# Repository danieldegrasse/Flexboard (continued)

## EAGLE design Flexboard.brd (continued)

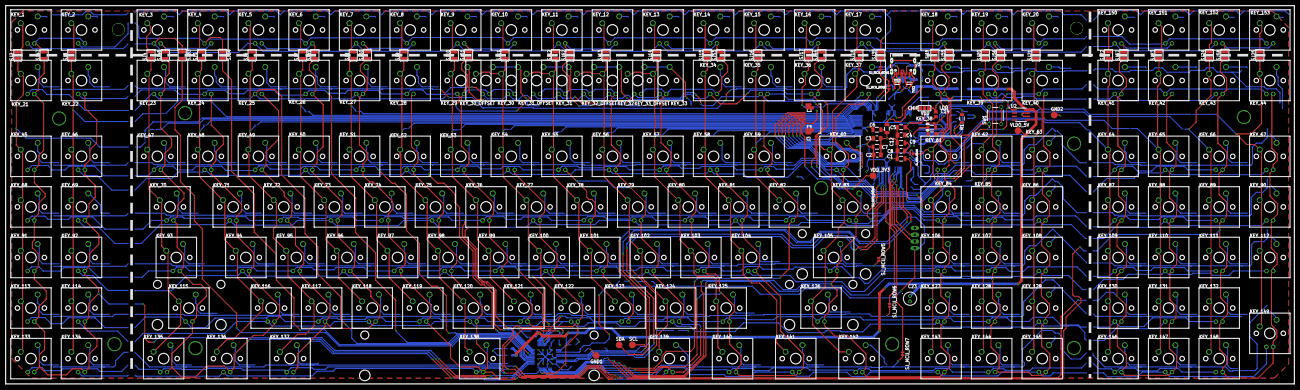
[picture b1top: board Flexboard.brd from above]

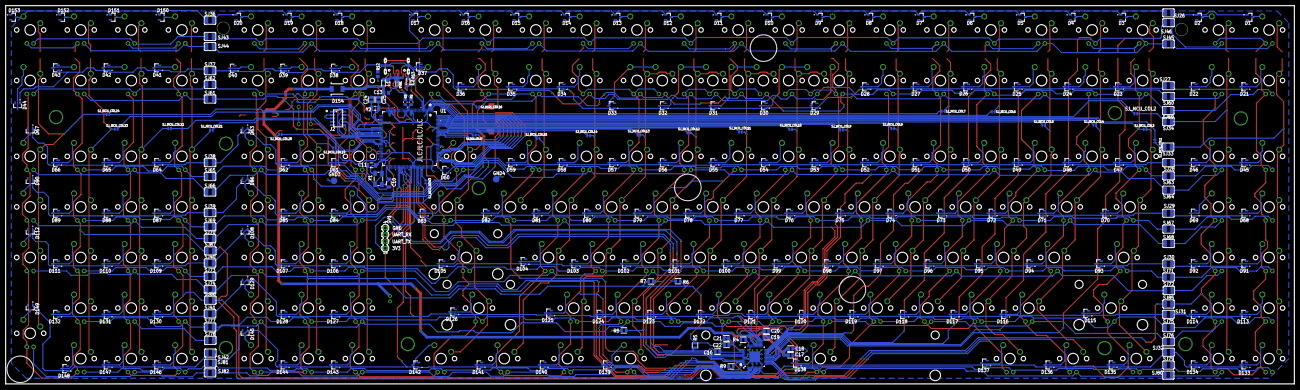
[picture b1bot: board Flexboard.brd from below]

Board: 2 copper layers, 485.5 x 142.5 mm, 498 parts (258 on the bottom side), 367 nets.

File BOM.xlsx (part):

Part | Value | Device | Package | Description | AVAILABILITY | CATEGORY | COMMENT | CONFIGURATION_POLE-THROW | CONTACT_CURRENT_RATING | CPU | DESCRIPTION | DIGI-KEY_PART_NUMBER | EU_ROHS_COMPLIANCE | FLASHKB | MANUFACTURER | MANUFACTURER_PART_NUMBER | MAXFREQUENCY | MF | MP | MPN | OC_FARNELL | OC_NEWARK | OPERATING_TEMP | PACKAGE | PART_STATUS | PINCOUNT | POPULARITY | POWER_RATING | PRICE | PURCHASE-URL | RATING | RESISTANCE | ROHS_COMPLIANT | SERIES | SRAMKB | SUB-CATEGORY | THERMALLOSS | TOLERANCE | TP_SIGNAL_NAME | TYPE | VENDOR | VOLTAGE_RATING
C1 | 1000pF | C1206C102K1RACAUTO | CAPC3216X110N | Cap Ceramic 0.001uF 100V X7R 10% SMD 1206 125°C Plastic T/R Check availability | In Stock |  |  |  |  |  | 1000 pF ±10% 100V Ceramic Capacitor X7R 1206 (3216 Metric) |  |  |  |  |  |  | KEMET | C1206C102K1RACAUTO |  |  |  |  | 1206 KEMET |  |  |  |  | None | https://pricing.snapeda.com/search/part/C1206C102K1RACAUTO/?ref=eda
C2 | 1uF | GCM31MR71H105KA55L | CAPC3216X125N | None Check availability | In Stock |  |  |  |  |  | SMD Capacitor X7R(EIA) with Capacitance: 1.0uF Tol. 10%. Rated Voltage: 50Vdc |  |  |  |  |  |  | Murata | GCM31MR71H105KA55L |  |  |  |  | 1206 Murata |  |  |  |  | None | https://pricing.snapeda.com/search/part/GCM31MR71H105KA55L/?ref=eda
C3 | 1uF | GCM31MR71H105KA55L | CAPC3216X125N | None Check availability | In Stock |  |  |  |  |  | SMD Capacitor X7R(EIA) with Capacitance: 1.0uF Tol. 10%. Rated Voltage: 50Vdc |  |  |  |  |  |  | Murata | GCM31MR71H105KA55L |  |  |  |  | 1206 Murata |  |  |  |  | None | https://pricing.snapeda.com/search/part/GCM31MR71H105KA55L/?ref=eda
C4 | 1uF | GCM31MR71H105KA55L | CAPC3216X125N | None Check availability | In Stock |  |  |  |  |  | SMD Capacitor X7R(EIA) with Capacitance: 1.0uF Tol. 10%. Rated Voltage: 50Vdc |  |  |  |  |  |  | Murata | GCM31MR71H105KA55L |  |  |  |  | 1206 Murata |  |  |  |  | None | https://pricing.snapeda.com/search/part/GCM31MR71H105KA55L/?ref=eda
C5 | 100nF | C1206C104K5RAC7800 | CAPC3216X88N | Cap Ceramic 0.1uF 50V X7R 10% SMD 1206 125C Plastic T/R Check availability | In Stock |  |  |  |  |  | 0.1 µF ±10% 50V Ceramic Capacitor X7R 1206 (3216 Metric) |  |  |  |  |  |  | KEMET | C1206C104K5RAC7800 |  |  |  |  | 3216 KEMET |  |  |  |  | None | https://pricing.snapeda.com/search/part/C1206C104K5RAC7800/?ref=eda
C6 | 100nF | C1206C104K5RAC7800 | CAPC3216X88N | Cap Ceramic 0.1uF 50V X7R 10% SMD 1206 125C Plastic T/R Check availability | In Stock |  |  |  |  |  | 0.1 µF ±10% 50V Ceramic Capacitor X7R 1206 (3216 Metric) |  |  |  |  |  |  | KEMET | C1206C104K5RAC7800 |  |  |  |  | 3216 KEMET |  |  |  |  | None | https://pricing.snapeda.com/search/part/C1206C104K5RAC7800/?ref=eda
C7 | 100nF | C1206C104K5RAC7800 | CAPC3216X88N | Cap Ceramic 0.1uF 50V X7R 10% SMD 1206 125C Plastic T/R Check availability | In Stock |  |  |  |  |  | 0.1 µF ±10% 50V Ceramic Capacitor X7R 1206 (3216 Metric) |  |  |  |  |  |  | KEMET | C1206C104K5RAC7800 |  |  |  |  | 3216 KEMET |  |  |  |  | None | https://pricing.snapeda.com/search/part/C1206C104K5RAC7800/?ref=eda
C8 | 1uF | GCM31MR71H105KA55L | CAPC3216X125N | None Check availability | In Stock |  |  |  |  |  | SMD Capacitor X7R(EIA) with Capacitance: 1.0uF Tol. 10%. Rated Voltage: 50Vdc |  |  |  |  |  |  | Murata | GCM31MR71H105KA55L |  |  |  |  | 1206 Murata |  |  |  |  | None | https://pricing.snapeda.com/search/part/GCM31MR71H105KA55L/?ref=eda
C9 | 100nF | C1206C104K5RAC7800 | CAPC3216X88N | Cap Ceramic 0.1uF 50V X7R 10% SMD 1206 125C Plastic T/R Check availability | In Stock |  |  |  |  |  | 0.1 µF ±10% 50V Ceramic Capacitor X7R 1206 (3216 Metric) |  |  |  |  |  |  | KEMET | C1206C104K5RAC7800 |  |  |  |  | 3216 KEMET |  |  |  |  | None | https://pricing.snapeda.com/search/part/C1206C104K5RAC7800/?ref=eda
C10 | 22pF | C1206C220JGGAC7800 | CAPC3216X110N | Check availability | In Stock |  |  |  |  |  | CAP CER 22PF 2KV NP0 1206 |  |  |  |  |  |  | KEMET | C1206C220JGGAC7800 |  |  |  |  | 3216 KEMET |  |  |  |  | None
C11 | 22pF | C1206C220JGGAC7800 | CAPC3216X110N | Check availability | In Stock |  |  |  |  |  | CAP CER 22PF 2KV NP0 1206 |  |  |  |  |  |  | KEMET | C1206C220JGGAC7800 |  |  |  |  | 3216 KEMET |  |  |  |  | None
C12 | 2.2uF | 1206ZC225MAT2A | CAPC3216X178N | CERAMIC CAPACITOR, 2.2UF, 10V, X7R, 20%, 1206, FULL REEL Check availability | In Stock |  |  |  |  |  | 2.2 µF ±20% 10V Ceramic Capacitor X7R 1206 (3216 Metric) |  |  |  |  |  |  | AVX | 1206ZC225MAT2A |  |  |  |  | 3216 AVX |  |  |  |  | None | https://pricing.snapeda.com/search/part/1206ZC225MAT2A/?ref=eda
C13 | 10uF | GRM21BC8YA106ME11L | CAPC2012X145N | Cap Ceramic 10uF 35V X6S 20% Pad SMD 0805 105C T/R |  |  |  |  |  |  | 0805 10 uF 35 V ±20% Tolerance X6S Multilayer Ceramic Capacitor | 490-10505-2-ND |  |  |  |  |  | Murata | GRM21BC8YA106ME11L |  |  |  |  | 2012 Murata |  |  |  |  |  | https://pricing.snapeda.com/search/part/GRM21BC8YA106ME11L/?ref=eda
C14 | 10uF | GRM21BC8YA106ME11L | CAPC2012X145N | Cap Ceramic 10uF 35V X6S 20% Pad SMD 0805 105C T/R |  |  |  |  |  |  | 0805 10 uF 35 V ±20% Tolerance X6S Multilayer Ceramic Capacitor | 490-10505-2-ND |  |  |  |  |  | Murata | GRM21BC8YA106ME11L |  |  |  |  | 2012 Murata |  |  |  |  |  | https://pricing.snapeda.com/search/part/GRM21BC8YA106ME11L/?ref=eda
C15 | 1000pF | C1206C102K1RACAUTO | CAPC3216X110N | Cap Ceramic 0.001uF 100V X7R 10% SMD 1206 125°C Plastic T/R Check availability | In Stock |  |  |  |  |  | 1000 pF ±10% 100V Ceramic Capacitor X7R 1206 (3216 Metric) |  |  |  |  |  |  | KEMET | C1206C102K1RACAUTO |  |  |  |  | 1206 KEMET |  |  |  |  | None | https://pricing.snapeda.com/search/part/C1206C102K1RACAUTO/?ref=eda
C16 | 0.47uF | C_CHIP-0805(2012-METRIC) | CAPC2012X110 | Capacitor - Generic |  | Capacitor
C17 | 0.47uF | C_CHIP-0805(2012-METRIC) | CAPC2012X110 | Capacitor - Generic |  | Capacitor
C18 | 0.1uF | C_CHIP-0805(2012-METRIC) | CAPC2012X110 | Capacitor - Generic |  | Capacitor
C19 | 0.47uF | C_CHIP-0805(2012-METRIC) | CAPC2012X110 | Capacitor - Generic |  | Capacitor
C20 | 0.1uF | C_CHIP-0805(2012-METRIC) | CAPC2012X110 | Capacitor - Generic |  | Capacitor
C21 | 0.47uF | C_CHIP-0805(2012-METRIC) | CAPC2012X110 | Capacitor - Generic |  | Capacitor
C22 | 0.1uF | C_CHIP-0805(2012-METRIC) | CAPC2012X110 | Capacitor - Generic |  | Capacitor
C23 | 22uF | 860020672011 | 860020672011 | 22uF 50V Electrolytic Capacitor Wurth 860020672011
C24 | 12pF | C_CHIP-0805(2012-METRIC) | CAPC2012X110 | Capacitor - Generic |  | Capacitor
C25 | 12pF | C_CHIP-0805(2012-METRIC) | CAPC2012X110 | Capacitor - Generic |  | Capacitor
D1 | BAS16LT3G | BAS16LT3G | SOT95P240X111-3N | Diode Small Signal Switching 100V 0.2A Automotive 3-Pin SOT-23 T/R Check prices | In Stock |  |  |  |  |  | Diode Standard 100V 200mA (DC) Surface Mount SOT-23-3 (TO-236) |  |  |  |  |  |  | ON Semiconductor | BAS16LT3G |  |  |  |  | SOT-23-3 ON Semiconductor |  |  |  |  | None
D2 | BAS16LT3G | BAS16LT3G | SOT95P240X111-3N | Diode Small Signal Switching 100V 0.2A Automotive 3-Pin SOT-23 T/R Check prices | In Stock |  |  |  |  |  | Diode Standard 100V 200mA (DC) Surface Mount SOT-23-3 (TO-236) |  |  |  |  |  |  | ON Semiconductor | BAS16LT3G |  |  |  |  | SOT-23-3 ON Semiconductor |  |  |  |  | None
D3 | BAS16LT3G | BAS16LT3G | SOT95P240X111-3N | Diode Small Signal Switching 100V 0.2A Automotive 3-Pin SOT-23 T/R Check prices | In Stock |  |  |  |  |  | Diode Standard 100V 200mA (DC) Surface Mount SOT-23-3 (TO-236) |  |  |  |  |  |  | ON Semiconductor | BAS16LT3G |  |  |  |  | SOT-23-3 ON Semiconductor |  |  |  |  | None
D4 | BAS16LT3G | BAS16LT3G | SOT95P240X111-3N | Diode Small Signal Switching 100V 0.2A Automotive 3-Pin SOT-23 T/R Check prices | In Stock |  |  |  |  |  | Diode Standard 100V 200mA (DC) Surface Mount SOT-23-3 (TO-236) |  |  |  |  |  |  | ON Semiconductor | BAS16LT3G |  |  |  |  | SOT-23-3 ON Semiconductor |  |  |  |  | None
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
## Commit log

2021-07-25 Initial Commmit: Laid out keys in schematic
2021-07-25 Partially routed schematic. Pattern should duplicate for rest of board.
2021-07-26 Finished schematic wiring for PCB
2021-07-28 Switches laid out, some alignment needs fixing
2021-07-28 Fixed switch alignments
2021-07-28 Routed columns
2021-07-28 Added first few row routes
2021-08-05 Finished routing keyboard switches and diodes
2021-10-04 Routed LED ROW nets
    PCB has not had led traces routed, but LED row nets are routed in
    schematic
2021-10-04 Routed Column Nets for LEDs
    No LED traces routed on board, but all nets are routed for columns and
    rows in schematic
2021-10-04 Solder joints for LEDs laid out on board
2021-10-04 Working on moving rows to bottom layer
2021-10-04 Revert "Working on moving rows to bottom layer"
    This reverts commit 131a86a1cb6fe059613502008a9fd4c9c1a2df1a.
    Decided it was best to leave diodes on top, so that the chip would have
    more space to route in
2021-10-04 Routed LED columns, rows partially routed
2021-10-05 Finished routed LEDs on PCB
2021-10-05 Starting designing trace routing to MCU
2021-10-06 Most columns are routed near the MCU
2021-10-07 Fixed offset keys
    Offset function row keys were offset one key to the right. They are now
    correctly lined up so the breaks between each block of function keys are
    at the right location
2021-10-07 Flipped Column and Row Trace Sides
    Column traces moved to front of board, row traces on rear. This way
    all SMD components are on rear of board.
2021-10-07 Lined up all Solder jumpers on their cut points
2021-10-09 Fixed net naming to use one indexing for rows and columns
    Also fixed naming so that the row wires routed to MCU have useful names
2021-10-09 All traces are now routed near mcu
2021-10-26 Assigned all keyboard traces to pins on MCU
    All traces for columns and rows now have initial pin assignments
2021-11-21 Added jumpers on each column and row trace
    Column and row traces now have jumpers, which are normally
    closed. These jumpers can be used to fix any routing errors,
    by cutting the jumper and patching wires.
2021-11-21 All column and row traces routed to MCU
    All column and row traces are connected to the MCU
2022-02-20 Added usb to MCU and routed power planes
    Added board wide power and ground planes, as well as USB traces to kinetis MCU.
2022-02-24 Routed diodes around usb
    All required diodes and solder bridges for keys are now routed to MCU
2022-03-03 Added decoupling capacitors around the mcu
    added power caps to MCU, 1uF and 100nF
2022-03-04 added oscillators to design
    added 8MHz and 32KHz crystals to design. Still need to add capacitors
    and resistors for USB 5V as well as DP/DN
2022-03-05 added usb 33 ohm resistors
    Added 33 ohm resistors to usb traces, and redid length matching
2022-03-06 added TVS diodes for ESD protection and power source switch
    TVS diodes required for high voltage spike protection, power
    source switch will enable selection of LDO or internal regulator
2022-03-06 added LDO to design
    LDO added, now just need power decoupling caps and diodes
2022-03-12 added all power domain components
    Added schottky diode on 5V LDO power rail to protect LDO. Power domain
    routing should be complete.
2022-04-24 added four media keys
    added four additional media keys to board, and renumbered keys to
    perserve correct numbering sequence.
2022-04-24 added current limiting resistors to LED rows
    current limit resistors should limit LED network to 10mA across each
    LED, for a total of roughly 70mA sourced from the chip.
2022-04-24 cleaned up name locations on board
    cleaned up name locations on board silkscreen to ensure that there will
    not be overlap between board printing and solder pads
2022-05-10 Fixed ERC errors
    Fixed valid ERC errors, and approved remaining overlap warnings as
    nonissues
2022-05-28 ran DRC, fixed majority of errors
    Fixed majority of DRC errors for JLPCB design rules. Still need to
    check dimension and overlap errors on solder bridges.
2022-06-16 added board dimensions and approved remaining DRC issues
    added required board dimensions, and verified remaining DRC issues will
    not cause problems
2022-06-17 added mounting standoffs
    mounting standoffs added for stability
2022-06-23 Add files via upload
    Added standoff locations (blind and thru)
    Added stab mounts for Lshift, Rshift, Enter, must use plate mount stabs for backspace and numenter due to conflict with MCU and bottom right standoff, respectively
    Rearranged some wires to make room for holes
    Resized PCB to max dimensions based off case
2022-06-23 missed in earlier commit
2022-06-27 Updated jtag header location
    Updated jtag header location, and also added several solder bridges
2022-07-10 added 5.1k pulldown resistors to CC lines
    Added 5.1k pulldown resistors to CC lines, as required
    for USB-C connection detection for UFP/sink device
2022-07-14 board review completed: fixed some length matchings
    some length matchings weren't as good as they could be.
    Fixed these up to improve signal integrity.
2022-07-14 cleaned up schematic
    Cleaned up PCB schematic to be more print friendly
2023-01-02 matrix: removed LED routings
    Removed all LED routings. This is the first step in transitioning
    the keyboard from controlling LEDs using the MCU to using a dedicated
    LED controller IC.
2023-01-29 routed LED controller source and sink lines
    Routed LED controller source and sink lines. Note that due to
    updating to Autodesk Fusion, these files are backwards compatible
    exports from that program.
    Added JLCPCB DRC, as well as LED controller and LDO eagle libraries.
2023-03-07 Added gerber files, sent for production
    Added gerber files. The board updates here are generated from
    Fusion360, which was used to complete the remainder of this project.
2023-03-09 updated BOM with parts on hand
    Updated BOM with parts on hand prior to mouser order, to prevent
    ordering duplicate parts that aren't needed.
2023-06-17 board: added layout PDF
    Added layout PDF, to make component placement easier without opening
    layout editor.
